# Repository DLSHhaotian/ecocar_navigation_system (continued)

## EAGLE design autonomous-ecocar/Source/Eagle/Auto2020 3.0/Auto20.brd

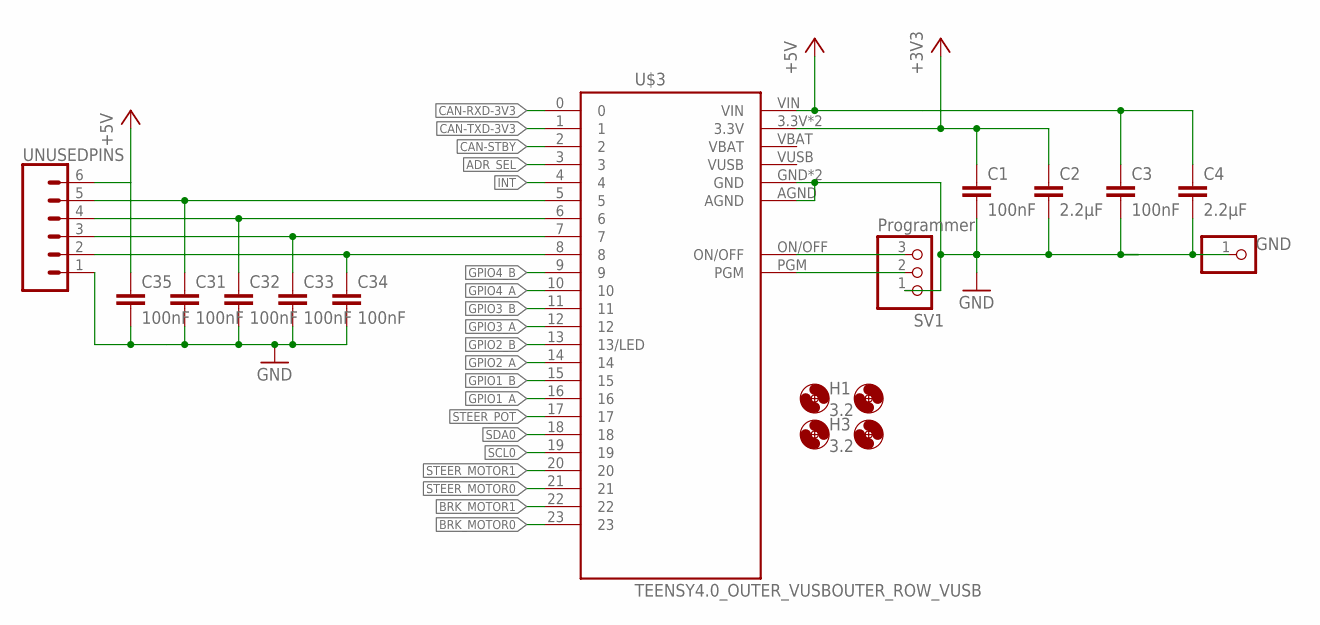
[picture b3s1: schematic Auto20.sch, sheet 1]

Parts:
C1, C3, C31, C32, C33, C34, C35: 100nF; RESC0805_L
C2, C4: 2.2µF; C1210
GND: PINHD-1X1; 1X01
H1, H2, H3, H4: 3.2; 3,2
SV1: Programmer; 1X03
U$3: TEENSY4.0_OUTER_VUSBOUTER_ROW_VUSB; TEENSY_4.0_OUTER_VUSB
UNUSEDPINS: CONN_06LOCK; 1X06_LOCK

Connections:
+3V3: C1.1, C2.1, U$3.3.3V, U$3.3.3V1 (3.3V); also elsewhere on the board
+5V: C3.1, C4.1, C35.1, U$3.VIN, UNUSEDPINS.6; also elsewhere on the board
ADR_SEL: U$3.3; also elsewhere on the board
BRK_MOTOR0: U$3.23; also elsewhere on the board
BRK_MOTOR1: U$3.22; also elsewhere on the board
CAN-RXD-3V3: U$3.0; also elsewhere on the board
CAN-STBY: U$3.2; also elsewhere on the board
CAN-TXD-3V3: U$3.1; also elsewhere on the board
GND: C1.2, C2.2, C3.2, C4.2, C31.2, C32.2, C33.2, C34.2, C35.2, GND.1, SV1.1, U$3.AGND, U$3.GND, U$3.GND1 (GND), UNUSEDPINS.1; also elsewhere on the board
GPIO1_A: U$3.16; also elsewhere on the board
GPIO1_B: U$3.15; also elsewhere on the board
GPIO2_A: U$3.14; also elsewhere on the board
GPIO2_B: U$3.13 (13/LED); also elsewhere on the board
GPIO3_A: U$3.12; also elsewhere on the board
GPIO3_B: U$3.11; also elsewhere on the board
GPIO4_A: U$3.10; also elsewhere on the board
GPIO4_B: U$3.9; also elsewhere on the board
INT: U$3.4; also elsewhere on the board
unnamed: C31.1, U$3.5, UNUSEDPINS.5
unnamed: SV1.3, U$3.ON/OFF
unnamed: SV1.2, U$3.PGM
unnamed: C32.1, U$3.6, UNUSEDPINS.4
unnamed: C33.1, U$3.7, UNUSEDPINS.3
unnamed: C34.1, U$3.8, UNUSEDPINS.2
SCL0: U$3.19; also elsewhere on the board
SDA0: U$3.18; also elsewhere on the board
STEER_MOTOR0: U$3.21; also elsewhere on the board
STEER_MOTOR1: U$3.20; also elsewhere on the board
STEER_POT: U$3.17; also elsewhere on the board

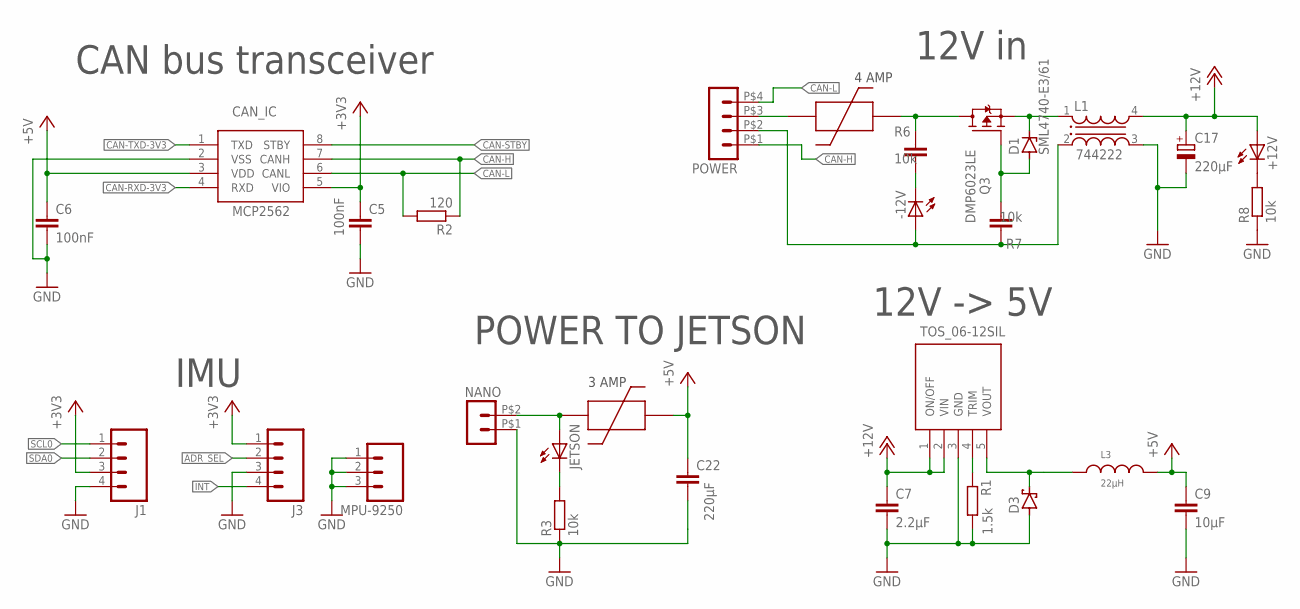
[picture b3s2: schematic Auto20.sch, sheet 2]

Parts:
+12V: LEDSMT1206; 1206
-12V: LEDSMT1206; 1206
C5, C6: 100nF; RESC0805_L
C7: 2.2µF; C1210
C9: 10µF; C1210
C17: 220µF; PANASONIC_E
C22: 220µF; C1210
CAN_IC: MCP2562; SOIC127P600X175-8
D1: SML4740-E3/61; DO214AC
D3: SBR1U150SA; DO214AC
IC1: TOS_06-12SIL; TOS-06-12SIL-6A
J1, J3: M04PTH; 1X04
JETSON: LEDSMT1206; 1206
L1: 744222; WE-SL2
L3: 22µH; WE-PD_7332/7345_PLASTIC_BASE
MPU-9250: M03PTH; 1X03
NANO: HEADER_POS2_43045-0200; 43045-0200
POWER: HEADER_POS4_43045-0401; 43045-0400
Q3: DMP6023LE; SOT223
R1: 1.5k; R0805
R2: 120; R0603
R3, R8: 10k; R0805
R6, R7: 10k; RESC0805_L
U$1, U$2: SMF_OMNI-BLOK_FUSE_BLOCK

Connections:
+3V3: C5.1, CAN_IC.5 (VIO), J1.3, J3.1; also elsewhere on the board
+5V: C6.1, C9.1, C22.1, CAN_IC.3 (VDD), L3.2, U$1.PIN2; also elsewhere on the board
+12V: +12V.A, C7.1, C17.+, IC1.1 (ON/OFF), IC1.2 (VIN), L1.4 (2)
ADR_SEL: J3.2; also elsewhere on the board
CAN-H: CAN_IC.7 (CANH), POWER.P$1 (1), R2.1
CAN-L: CAN_IC.6 (CANL), POWER.P$4 (4), R2.2
CAN-RXD-3V3: CAN_IC.4 (RXD); also elsewhere on the board
CAN-STBY: CAN_IC.8 (STBY); also elsewhere on the board
CAN-TXD-3V3: CAN_IC.1 (TXD); also elsewhere on the board
GND: C5.2, C6.2, C7.2, C9.2, C17.-, C22.2, CAN_IC.2 (VSS), D3.A, IC1.3 (GND), J1.4, J3.3, L1.3, MPU-9250.1, MPU-9250.2, MPU-9250.3, NANO.P$1 (1), R1.2, R3.1, R8.1; also elsewhere on the board
INT: J3.4; also elsewhere on the board
unnamed: D3.C, IC1.5 (VOUT), L3.1
unnamed: POWER.P$3 (3), U$2.PIN1
unnamed: IC1.4 (TRIM), R1.1
unnamed: JETSON.C, R3.2
unnamed: JETSON.A, NANO.P$2 (2), U$1.PIN1
unnamed: D1.C, L1.1, Q3.3 (S)
unnamed: -12V.A, L1.2 (4), POWER.P$2 (2), R7.1
unnamed: Q3.2 (D), Q3.4 (D), R6.1, U$2.PIN2
unnamed: D1.A, Q3.1 (G), R7.2
unnamed: -12V.C, R6.2
unnamed: +12V.C, R8.2
SCL0: J1.1; also elsewhere on the board
SDA0: J1.2; also elsewhere on the board

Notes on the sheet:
CAN bus transceiver
12V in
12V -> 5V
IMU
POWER TO JETSON
3 AMP
4 AMP

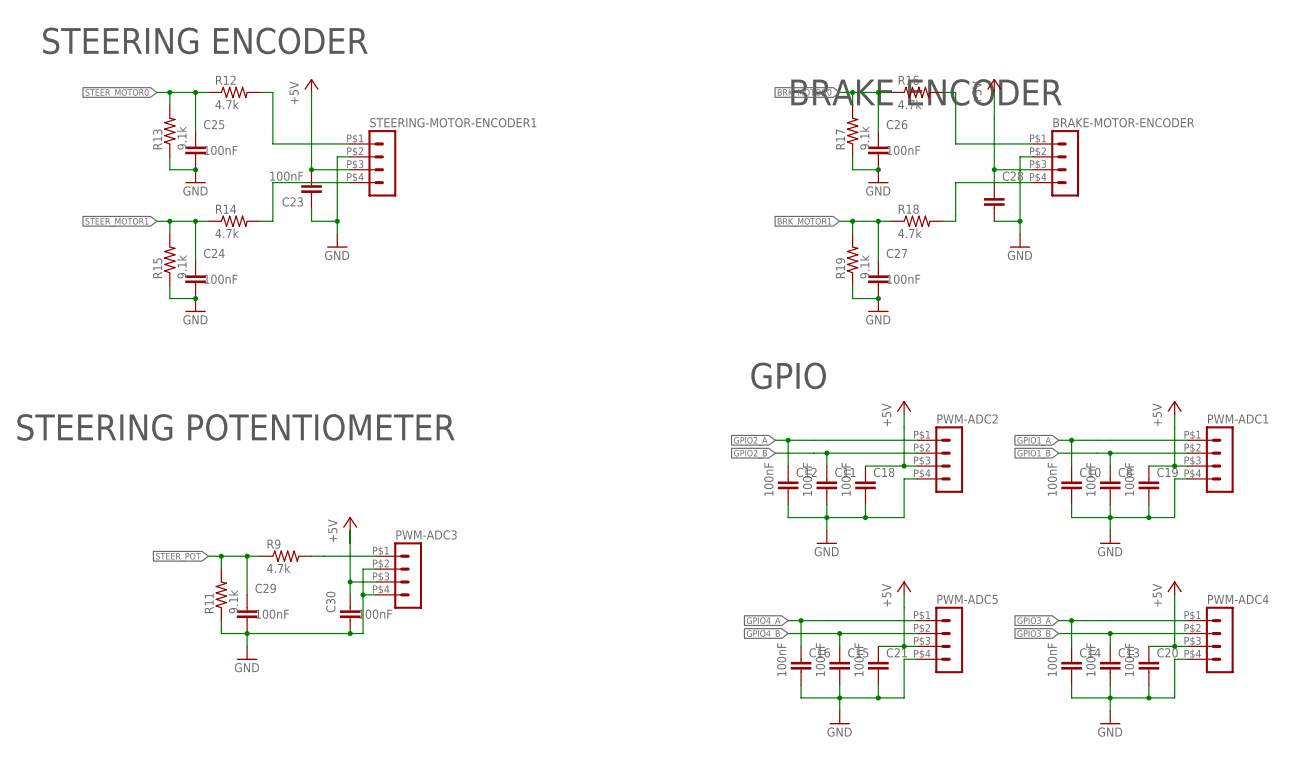
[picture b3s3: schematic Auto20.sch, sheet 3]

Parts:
BRAKE-MOTOR-ENCODER: HEADER_POS4_43045-0401; 43045-0400
C8, C10, C11, C12, C13, C14, C15, C16, C18, C19, C20, C21, C23, C24, C25, C26, C27, C28, C29, C30: 100nF; RESC0805_L
PWM-ADC1, PWM-ADC2, PWM-ADC3, PWM-ADC4, PWM-ADC5: HEADER_POS4_43045-0401; 43045-0400
R9, R12, R14, R16, R18: 4.7k; 0805
R11, R13, R15, R17, R19: 9.1k; 0805
STEERING-MOTOR-ENCODER1: HEADER_POS4_43045-0401; 43045-0400

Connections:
+5V: BRAKE-MOTOR-ENCODER.P$3 (3), C18.1, C19.1, C20.1, C21.1, C23.2, C28.1, C30.1, PWM-ADC1.P$3 (3), PWM-ADC2.P$3 (3), PWM-ADC3.P$3 (3), PWM-ADC4.P$3 (3), PWM-ADC5.P$3 (3), STEERING-MOTOR-ENCODER1.P$3 (3); also elsewhere on the board
ADC3-RAW: PWM-ADC3.P$1 (1), R9.2
ADC9-RAW: BRAKE-MOTOR-ENCODER.P$4 (4), R18.2
ADC9-RAW1: R14.2, STEERING-MOTOR-ENCODER1.P$4 (4)
BRK_MOTOR0: C26.1, R16.1, R17.2; also elsewhere on the board
BRK_MOTOR1: C27.1, R18.1, R19.2; also elsewhere on the board
GND: BRAKE-MOTOR-ENCODER.P$2 (2), C8.2, C10.2, C11.2, C12.2, C13.2, C14.2, C15.2, C16.2, C18.2, C19.2, C20.2, C21.2, C23.1, C24.2, C25.2, C26.2, C27.2, C28.2, C29.2, C30.2, PWM-ADC1.P$4 (4), PWM-ADC2.P$4 (4), PWM-ADC3.P$2 (2), PWM-ADC3.P$4 (4), PWM-ADC4.P$4 (4), PWM-ADC5.P$4 (4), R11.1, R13.1, R15.1, R17.1, R19.1, STEERING-MOTOR-ENCODER1.P$2 (2); also elsewhere on the board
GPIO1_A: C10.1, PWM-ADC1.P$1 (1); also elsewhere on the board
GPIO1_B: C8.1, PWM-ADC1.P$2 (2); also elsewhere on the board
GPIO2_A: C12.1, PWM-ADC2.P$1 (1); also elsewhere on the board
GPIO2_B: C11.1, PWM-ADC2.P$2 (2); also elsewhere on the board
GPIO3_A: C14.1, PWM-ADC4.P$1 (1); also elsewhere on the board
GPIO3_B: C13.1, PWM-ADC4.P$2 (2); also elsewhere on the board
GPIO4_A: C16.1, PWM-ADC5.P$1 (1); also elsewhere on the board
GPIO4_B: C15.1, PWM-ADC5.P$2 (2); also elsewhere on the board
unnamed: BRAKE-MOTOR-ENCODER.P$1 (1), R16.2
unnamed: R12.2, STEERING-MOTOR-ENCODER1.P$1 (1)
STEER_MOTOR0: C25.1, R12.1, R13.2; also elsewhere on the board
STEER_MOTOR1: C24.1, R14.1, R15.2; also elsewhere on the board
STEER_POT: C29.1, R9.1, R11.2; also elsewhere on the board

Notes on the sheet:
BRAKE ENCODER
STEERING ENCODER
STEERING POTENTIOMETER
GPIO

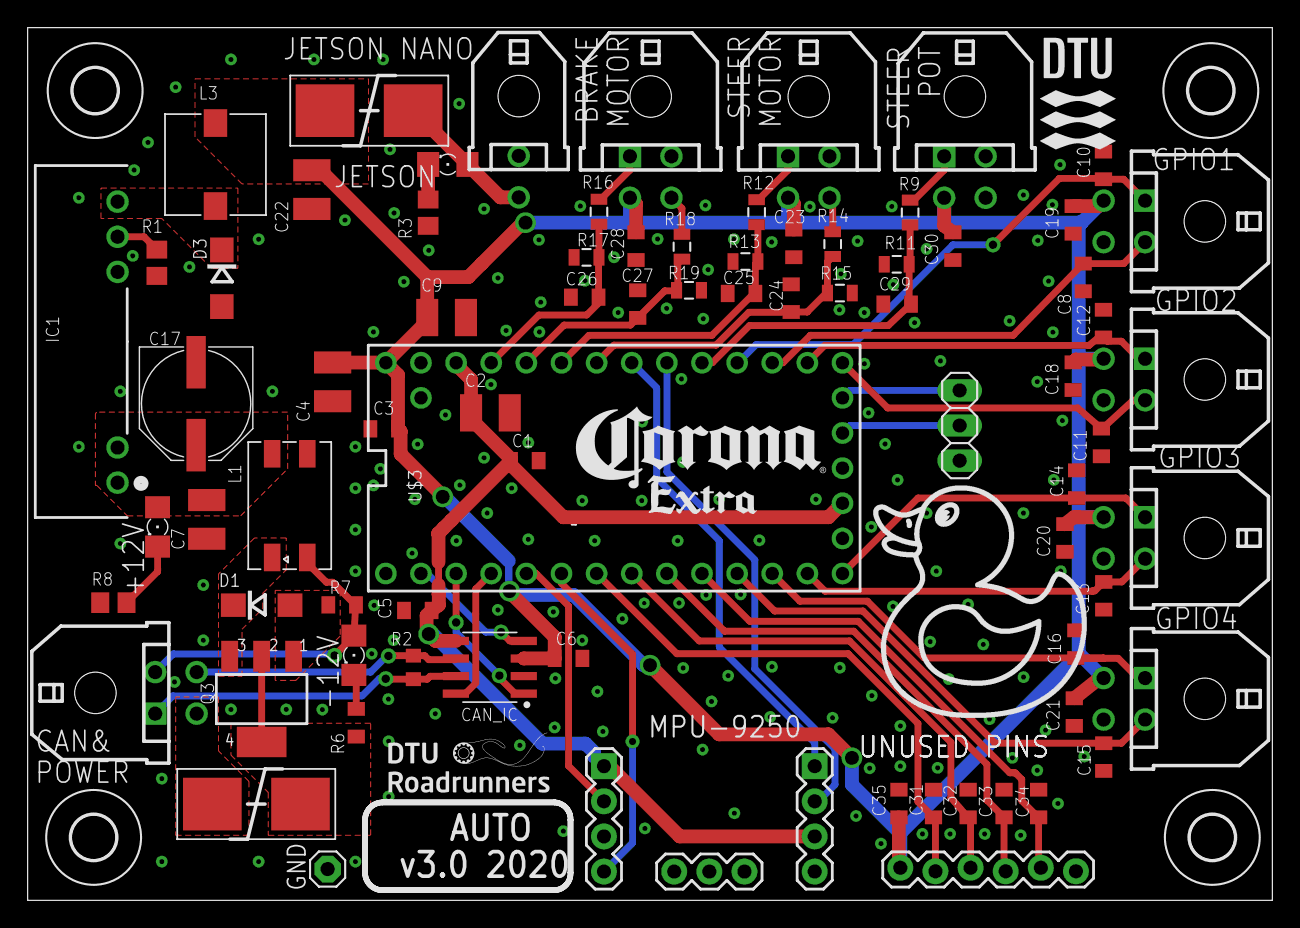
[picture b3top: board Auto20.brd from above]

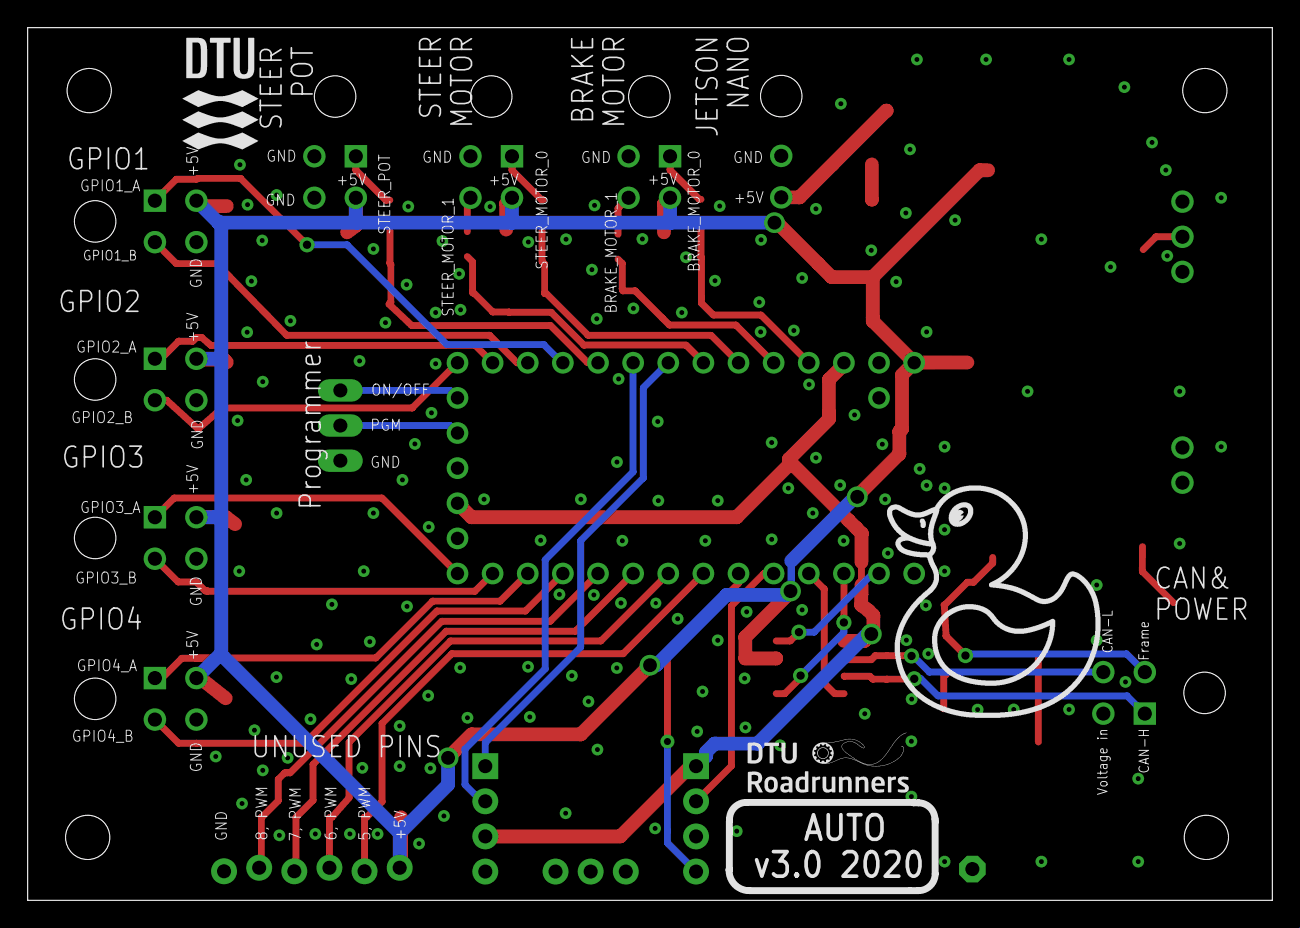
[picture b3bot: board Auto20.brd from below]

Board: 2 copper layers, 90.0 x 63.1 mm, 90 parts (3 on the bottom side), 48 nets.

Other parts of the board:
U$4: CORONA
U$5, U$8: RUBBERDUCK
U$6, U$14: ROADRUNNERS-FULL
U$10, U$13: DTU-SMALL-5MM

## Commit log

2020-09-20 wrote a readme file
2020-09-20 add distributed
2020-09-20 costmap_base.h writing
2020-09-21 costmap_base end; layer end;manager writing
2020-09-22 plugin1 writing
2020-09-23 obstacleLayer writing
2020-09-26 obstacle finished
2020-09-29 success moveit with gazebo especially with controller
2020-10-02 costmap_system finished
2020-10-05 close the hand
2020-10-06 pick once success!
2020-10-06 finished but not completed
2020-10-06 launch file added
2020-10-10 finished
2020-10-12 threshold changed
2020-10-18 costmap_2d used
2020-11-03 backup
2020-11-06 distance local map finished
2020-11-21 lattice planner
2020-11-22 22/11/2020
2020-11-26 global goal point added
2020-11-27 lattice planner worked!
2023-08-06 update source code
2023-08-06 Create LICENSE
2023-08-06 update report
